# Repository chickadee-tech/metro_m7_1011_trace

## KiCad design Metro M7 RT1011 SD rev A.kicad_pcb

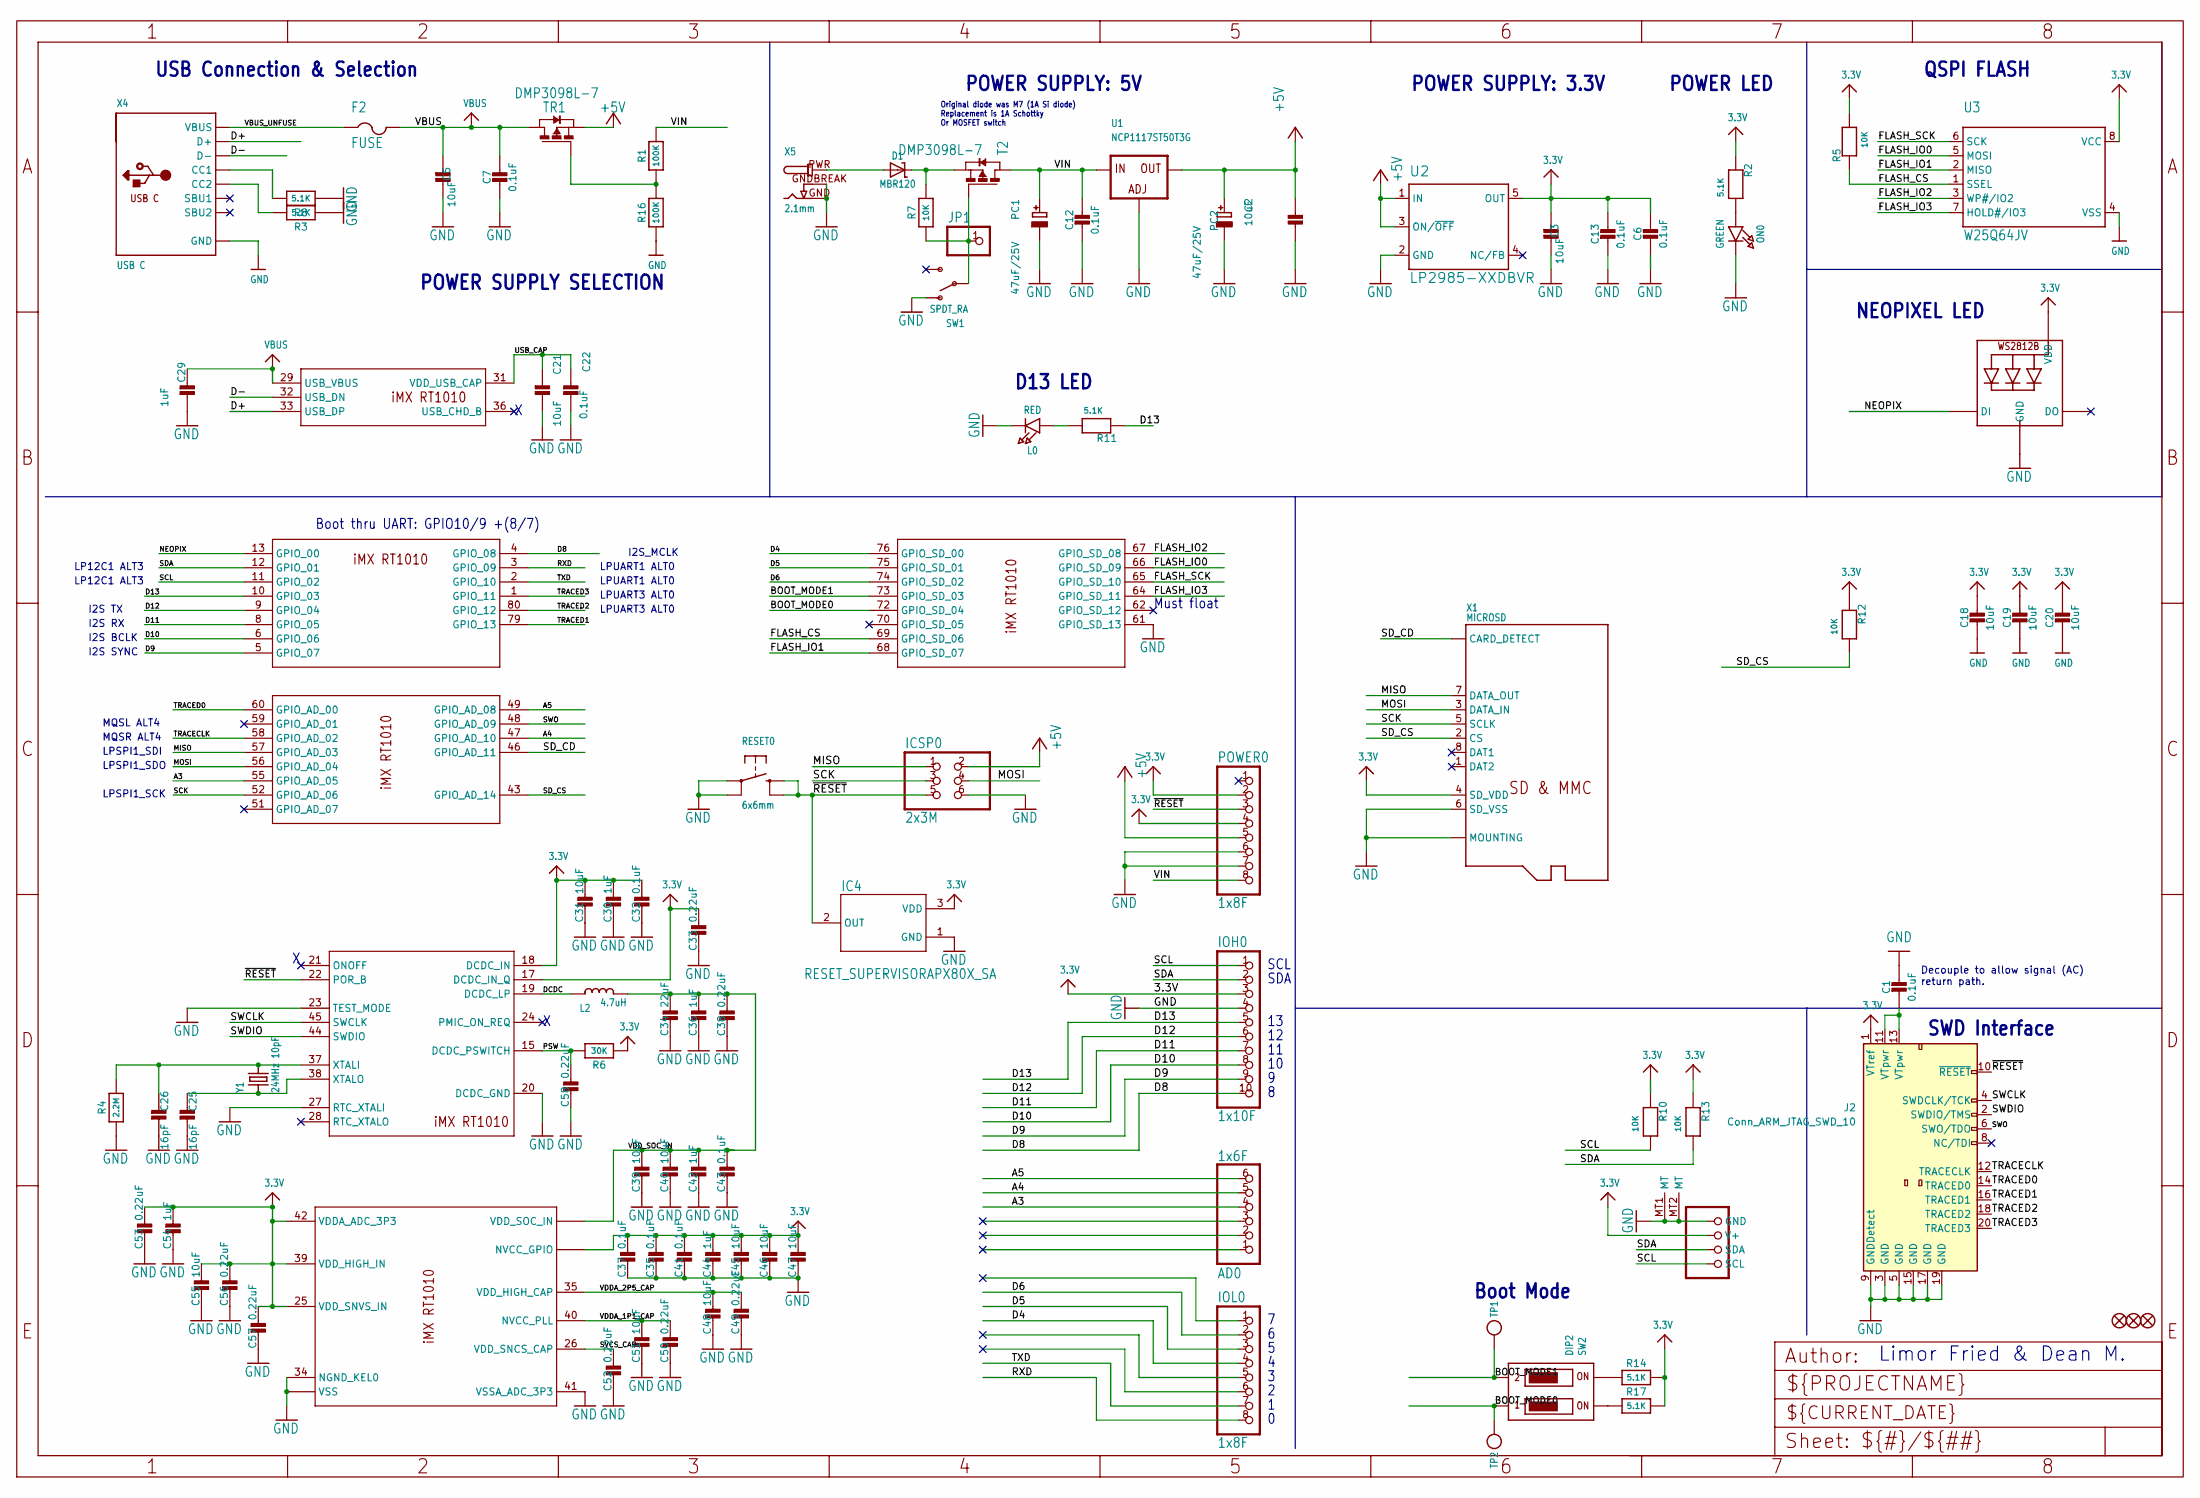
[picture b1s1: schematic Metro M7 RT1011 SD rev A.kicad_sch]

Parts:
AD0: 1x6F; 1X06_OVALWAVE
C1, C6, C7, C12, C13, C22, C32, C35, C37, C41, C43: 0.1uF; 0603-NO
C2, C3, C5, C18, C19, C20, C21, C31, C39, C40, C45, C46, C47, C48, C51, C55: 10uF; 0805-NO
C25, C26: 16pF; 0603-NO
C29, C30, C36, C42, C44, C54: 1uF; 0603-NO
C33, C38, C49, C50, C52, C53, C56, C57, C58: 0.22uF; 0603-NO
C34: 22uF; 0805-NO
CONN1: STEMMA_I2C_QT; JST_SH4
D1: MBR120; SOD-123
F2: FUSE; R1206
FD1, FD2, FD3: FIDUCIAL_1MM
IC2: IMX_RT1010; QFP50P1400X1400X160-80N
IC4: RESET_SUPERVISORAPX80X_SA; SOT23-WIDE
ICSP0: 2x3M; 2X03_ROUND_70MIL
IOH0: 1x10F; 1X10_OVALWAVE
IOL0: 1x8F; 1X08_OVALWAVE
J2: Conn_ARM_JTAG_SWD_10; PinHeader_2x10_P1.27mm_Vertical_SMD
JP1: HEADER-1X1ROUND; 1X01_ROUND
L0: RED; CHIPLED_0603_NOOUTLINE
L2: 4.7uH; INDUCTOR_1007
LED1: WS2812B_3535FULL; LED3535_FULLPADS
ON0: GREEN; CHIPLED_0603_NOOUTLINE
PC1, PC2: 47uF/25V; PANASONIC_D
POWER0: 1x8F; 1X08_OVALWAVE
R1, R16: 100K; 0603-NO
R2, R3, R8, R11, R14, R17: 5.1K; 0603-NO
R4: 2.2M; 0603-NO
R5, R7, R10, R12, R13: 10K; 0603-NO
R6: 30K; 0603-NO
RESET0: 6x6mm; 6MMX6MM_TACTILE_SMT
SW1: SPDT_RA; SPDT_SMT_SSSS811101
SW2: DIP2; DIPSWITCH_2PIN
T2: DMP3098L-7; SOT-23
TP1, TP2: TESTPOINTROUND1.5MM; TESTPOINT_ROUND_1.5MM
TR1: DMP3098L-7; SOT-23
U1: NCP1117ST50T3G; SOT223-R
U2: LP2985-XXDBVR; SOT23-DBV
U3: W25Q64JV; SOIC8_208MIL
X1: MICROSD
X4: USB C; USB_C_CUSB31-CFM2AX-01-X
X5: 2.1mm; DCJACK_2MM_PTH
Y1: 24MHz 10pF; CRYSTAL_2.5X2

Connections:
3.3V: C3.2, C6.2, C13.1, C18.1, C19.1, C20.1, C30.1, C31.1, C32.1, C33.1, C35.1, C37.1, C41.1, C44.1, C45.1, C46.1, C47.1, C53.1, C54.1, C55.1, C56.1, C57.1, CONN1.2 (V+), IC2.7 (NVCC_GPIO), IC2.17 (DCDC_IN_Q), IC2.18 (DCDC_IN), IC2.25 (VDD_SNVS_IN), IC2.39 (VDD_HIGH_IN), IC2.42 (VDDA_ADC_3P3), IC2.50 (NVCC_GPIO), IC2.63 (NVCC_GPIO), IC2.71 (NVCC_GPIO), IC4.3 (VDD), IOH0.3, J2.1 (VTref), LED1.2 (VDD), POWER0.2, POWER0.4, R2.1, R5.2, R6.1, R10.1, R12.1, R13.1, R14.2, R17.2, U2.5 (OUT), U3.8 (VCC), X1.4 (SD_VDD)
+5V: C2.2, ICSP0.2, PC2.+, POWER0.5, TR1.2 (S), U1.2 (OUT), U1.4 (OUT), U2.1 (IN), U2.3 (ON/~OFF)
/A3: AD0.4, IC2.55 (GPIO_AD_05)
/A4: AD0.5, IC2.47 (GPIO_AD_10)
/A5: AD0.6, IC2.49 (GPIO_AD_08)
/BOOT_MODE0: IC2.72 (GPIO_SD_04), SW2.1OFF, TP2.P$1
/BOOT_MODE1: IC2.73 (GPIO_SD_03), SW2.2OFF, TP1.P$1
/D4: IC2.76 (GPIO_SD_00), IOL0.4
/D5: IC2.75 (GPIO_SD_01), IOL0.3
/D6: IC2.74 (GPIO_SD_02), IOL0.2
/D8: IC2.4 (GPIO_08), IOH0.10
/D9: IC2.5 (GPIO_07), IOH0.9
/D10: IC2.6 (GPIO_06), IOH0.8
/D11: IC2.8 (GPIO_05), IOH0.7
/D12: IC2.9 (GPIO_04), IOH0.6
/D13: IC2.10 (GPIO_03), IOH0.5, R11.1
/D+: IC2.33 (USB_DP), X4.A6 (D+), X4.B6 (D+)
/D-: IC2.32 (USB_DN), X4.A7 (D-), X4.B7 (D-)
/DCDC: IC2.19 (DCDC_LP), L2.P$1 (1)
/FLASH_CS: IC2.69 (GPIO_SD_06), R5.1, U3.1 (SSEL)
/FLASH_IO0: IC2.66 (GPIO_SD_09), U3.5 (MOSI)
/FLASH_IO1: IC2.68 (GPIO_SD_07), U3.2 (MISO)
/FLASH_IO2: IC2.67 (GPIO_SD_08), U3.3 (WP#/IO2)
/FLASH_IO3: IC2.64 (GPIO_SD_11), U3.7 (HOLD#/IO3)
/FLASH_SCK: IC2.65 (GPIO_SD_10), U3.6 (SCK)
/MISO: IC2.57 (GPIO_AD_03), ICSP0.1, X1.7 (DATA_OUT)
/MOSI: IC2.56 (GPIO_AD_04), ICSP0.4, X1.3 (DATA_IN)
/NEOPIX: IC2.13 (GPIO_00), LED1.1 (DI)
/PSW: C58.1, IC2.15 (DCDC_PSWITCH), R6.2
/RXD: IC2.3 (GPIO_09), IOL0.8
/SCK: IC2.52 (GPIO_AD_06), ICSP0.3, X1.5 (SCLK)
/SCL: CONN1.4 (SCL), IC2.11 (GPIO_02), IOH0.1, R10.2
/SDA: CONN1.3 (SDA), IC2.12 (GPIO_01), IOH0.2, R13.2
/SD_CD: IC2.46 (GPIO_AD_11), X1.CD1 (CARD_DETECT), X1.CD2 (CARD_DETECT)
/SD_CS: IC2.43 (GPIO_AD_14), R12.2, X1.2 (CS)
/SVCS_CAP: C52.1, IC2.26 (VDD_SNCS_CAP)
/SWCLK: IC2.45 (SWCLK), J2.4 (SWDCLK/TCK)
/SWDIO: IC2.44 (SWDIO), J2.2 (SWDIO/TMS)
/SWO: IC2.48 (GPIO_AD_09), J2.6 (SWO/TDO)
/TRACECLK: IC2.58 (GPIO_AD_02), J2.12 (TRACECLK)
/TRACED0: IC2.60 (GPIO_AD_00), J2.14 (TRACED0)
/TRACED1: IC2.79 (GPIO_13), J2.16 (TRACED1)
/TRACED2: IC2.80 (GPIO_12), J2.18 (TRACED2)
/TRACED3: IC2.1 (GPIO_11), J2.20 (TRACED3)
/TXD: IC2.2 (GPIO_10), IOL0.7
/USB_CAP: C21.2, C22.1, IC2.31 (VDD_USB_CAP)
/VBUS_UNFUSE: F2.1, X4.A4B9 (VBUS), X4.B4A9 (VBUS)
/VDDA_1P1_CAP: C50.1, C51.1, IC2.40 (NVCC_PLL)
/VDDA_2P5_CAP: C48.1, C49.1, IC2.35 (VDD_HIGH_CAP)
/VDD_SOC_IN: C34.1, C36.1, C38.1, C39.1, C40.1, C42.1, C43.1, IC2.14 (VDD_SOC_IN), IC2.53 (VDD_SOC_IN), IC2.77 (VDD_SOC_IN), L2.P$2 (2)
/VIN: C12.1, PC1.+, POWER0.8, R1.2, T2.1 (D), U1.3 (IN)
/~RESET: IC2.22 (POR_B), IC4.2 (OUT), ICSP0.5, J2.10 (~RESET), POWER0.3, RESET0.B (S), RESET0.B' (S1)
GND: C1.1, C2.1, C3.1, C5.1, C6.1, C7.2, C12.2, C13.2, C18.2, C19.2, C20.2, C21.1, C22.2, C25.2, C26.2, C29.2, C30.2, C31.2, C32.2, C33.2, C34.2, C35.2, C36.2, C37.2, C38.2, C39.2, C40.2, C41.2, C42.2, C43.2, C44.2, C45.2, C46.2, C47.2, C48.2, C49.2, C50.2, C51.2, C52.2, C53.2, C54.2, C55.2, C56.2, C57.2, C58.2, CONN1.1 (GND), CONN1.MT1 (MT), CONN1.MT2 (MT), IC2.16 (VSS), IC2.20 (DCDC_GND), IC2.23 (TEST_MODE), IC2.27 (RTC_XTALI), IC2.30 (VSS), IC2.34 (NGND_KEL0), IC2.41 (VSSA_ADC_3P3), IC2.54 (VSS), IC2.61 (GPIO_SD_13), IC2.78 (VSS), IC4.1 (GND), ICSP0.6, IOH0.4, J2.3 (GND), J2.5 (GND), J2.9 (GNDDetect), J2.15 (GND), J2.17 (GND), J2.19 (GND), L0.C, LED1.4 (GND), ON0.C, PC1.-, PC2.-, POWER0.6, POWER0.7, R3.1, R4.1, R8.1, R16.1, RESET0.A, RESET0.A' (P1), SW1.A (O), U1.1 (ADJ), U2.2 (GND), U3.4 (VSS), X1.6 (SD_VSS), X1.MT1 (MOUNTING), X1.MT2 (MOUNTING), X4.A1B12 (GND), X4.B1A12 (GND), X5.GND, X5.GNDBREAK
unnamed: C1.2, J2.11 (VTpwr), J2.13 (VTpwr)
unnamed: D1.A, X5.PWR
unnamed: C26.1, IC2.37 (XTALI), R4.2, Y1.3 (2)
unnamed: C25.1, IC2.38 (XTALO), Y1.1
unnamed: L0.A, R11.2
unnamed: ON0.A, R2.2
unnamed: R14.1, SW2.2ON
unnamed: R17.1, SW2.1ON
unnamed: JP1.1, R7.1, SW1.B, T2.3 (G)
unnamed: D1.C, R7.2, T2.2 (S)
unnamed: R1.1, R16.2, TR1.3 (G)
unnamed: R8.2, X4.A5 (CC1)
unnamed: R3.2, X4.B5 (CC2)
VBUS: C5.2, C7.1, C29.1, F2.2, IC2.29 (USB_VBUS), TR1.1 (D)

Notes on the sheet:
LPUART1 ALT0
I2S_MCLK
Must float
POWER SUPPLY SELECTION
LPUART3 ALT0
LPSPI1_SDI
LPSPI1_SDO
Decouple to allow signal (AC) return path.
USB Connection & Selection
Original diode was M7 (1A Si diode) Replacement is 1A Schottky Or MOSFET switch
Boot Mode
I2S SYNC
LP12C1 ALT3
SCL
I2S BCLK
QSPI FLASH
I2S RX
D13 LED
MQSL ALT4
MQSR ALT4
Boot thru UART: GPIO10/9 +(8/7)
I2S TX
SWD Interface
POWER LED
NEOPIXEL LED
POWER SUPPLY: 5V
Limor Fried & Dean M.
LPSPI1_SCK
POWER SUPPLY: 3.3V
SDA

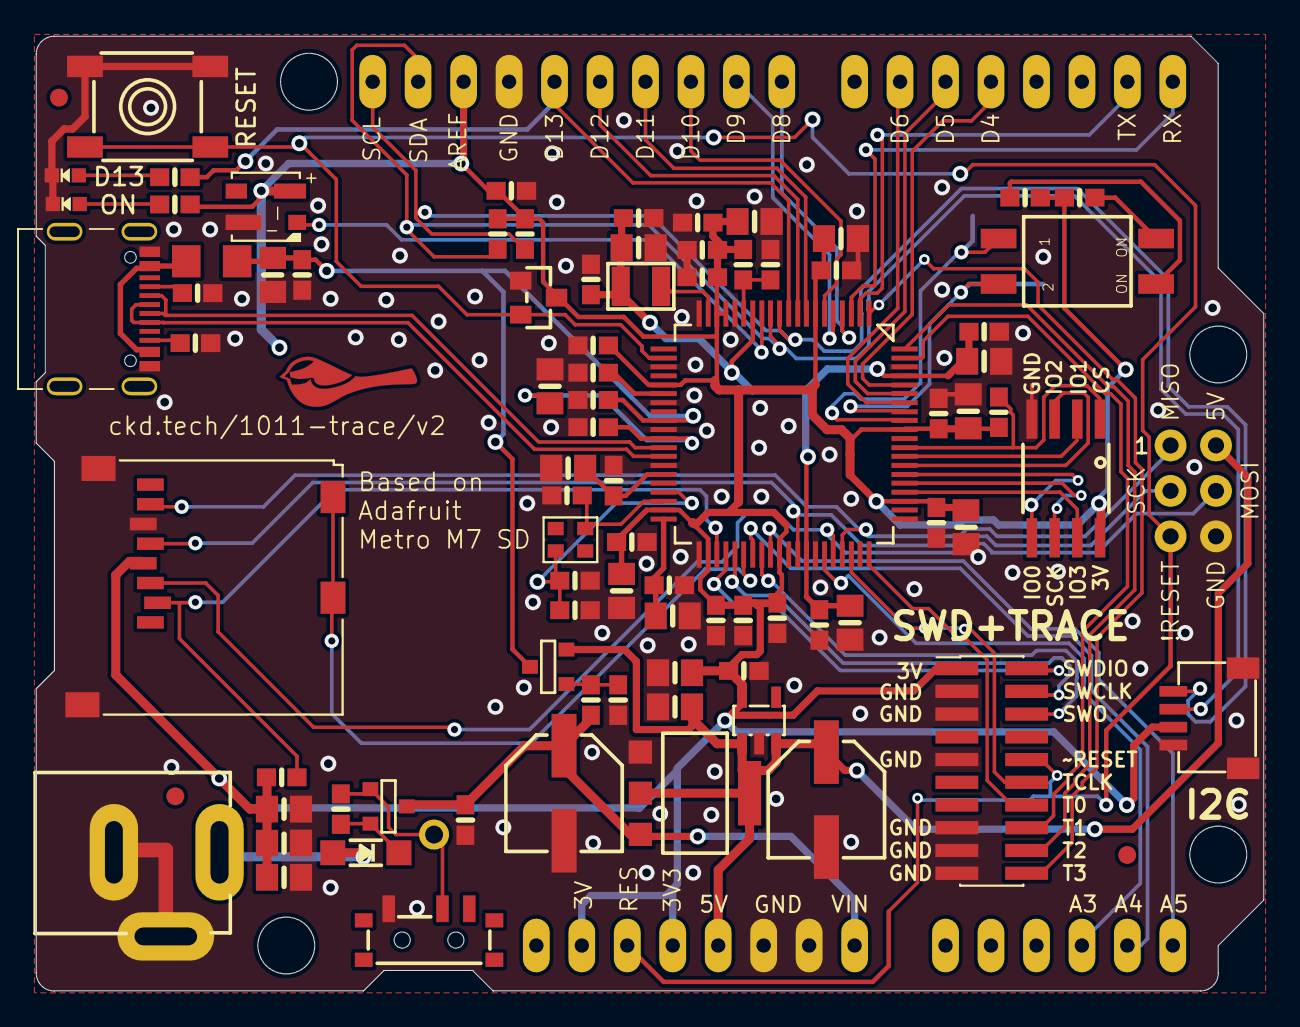
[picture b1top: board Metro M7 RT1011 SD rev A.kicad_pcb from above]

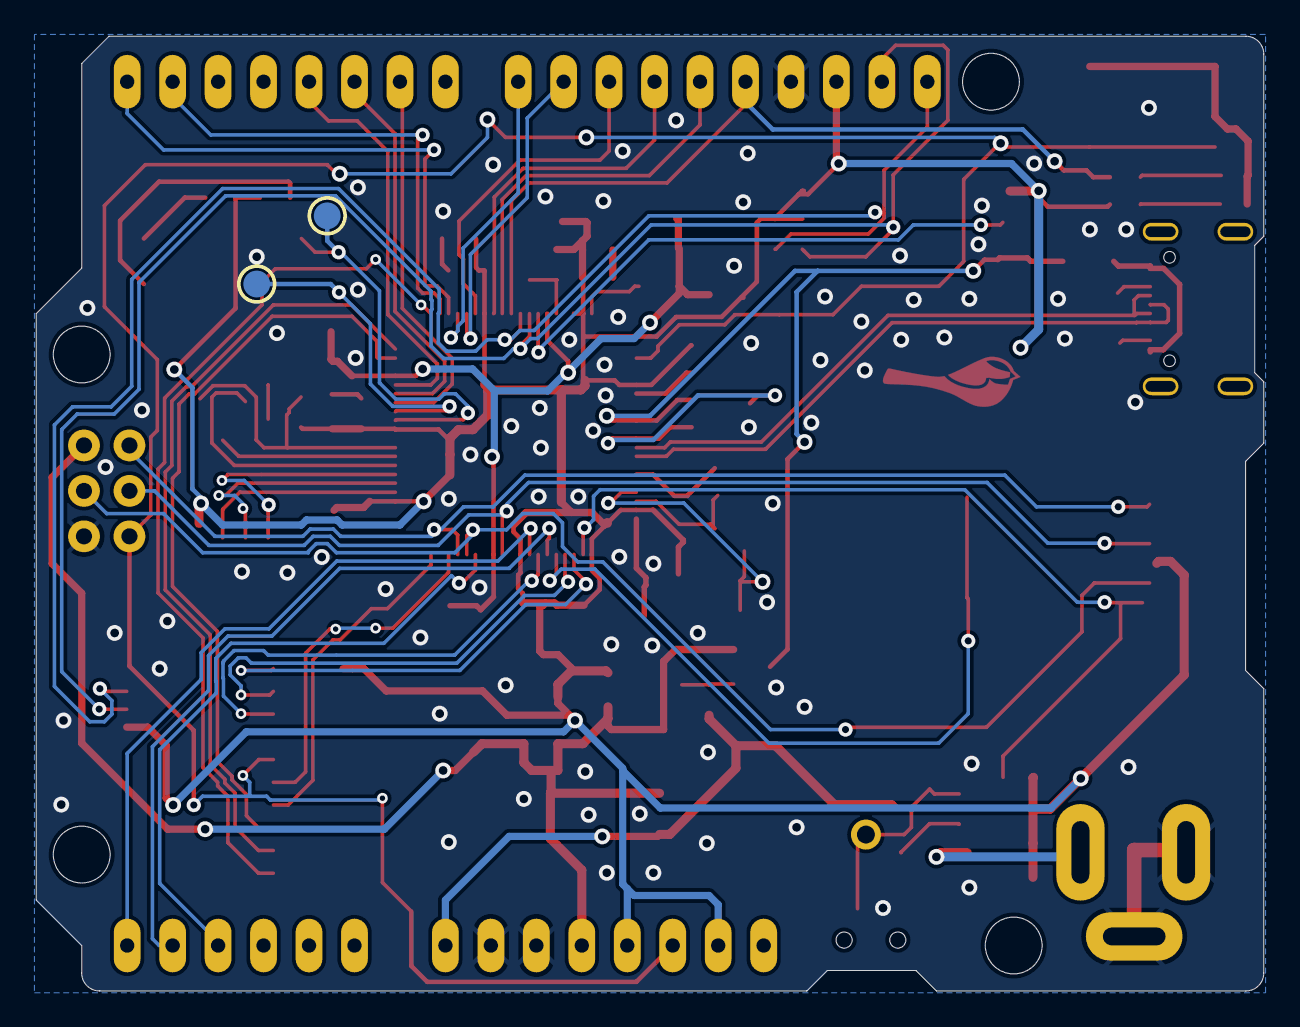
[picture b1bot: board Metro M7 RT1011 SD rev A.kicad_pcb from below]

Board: 2 copper layers, 68.6 x 53.3 mm, 100 parts (3 on the bottom side), 66 nets.

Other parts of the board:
@HOLE0, @HOLE1, @HOLE2, @HOLE3: (no value)
U$12: M7_RT1011SD_TOP
U$19: M7_RT1011SD_BOT

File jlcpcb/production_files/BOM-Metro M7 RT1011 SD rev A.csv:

Comment,Designator,Footprint,LCSC
30K,R6,0603-NO,C100001
SPDT_RA,SW1,SPDT_SMT_SSSS811101,C109335
MICROSD,X1,MICROSD,C125617
0.1uF,"C12,C13,C22,C32,C35,C37,C41,C43,C6,C7",0603-NO,C14663
DMP3098L-7,"T2,TR1",SOT-23,C150492
NCP1117ST50T3G,U1,SOT223-R,C156196
RESET_SUPERVISORAPX80X_SA,IC4,SOT23-WIDE,C156335
IMX_RT1010,IC2,QFP50P1400X1400X160-80N,C1575810
1uF,"C29,C30,C36,C42,C44,C54",0603-NO,C15849
10uF,"C18,C19,C2,C20,C21,C3,C31,C39,C40,C45,C46,C47,C48,C5,C51,C55",0805-NO,C15850
USB C,X4,USB_C_CUSB31-CFM2AX-01-X,C165948
0.22uF,"C33,C38,C49,C50,C52,C53,C56,C57,C58",0603-NO,C21120
4.7uH,L2,INDUCTOR_1007,C223195
RED,L0,CHIPLED_0603_NOOUTLINE,C2286
2.2M,R4,0603-NO,C22938
5.1K,"R11,R14,R17,R2,R3,R8",0603-NO,C23186
24MHz 10pF,Y1,CRYSTAL_2.5X2,C255953
100K,"R1,R16",0603-NO,C25803
10K,"R10,R12,R13,R5,R7",0603-NO,C25804
6x6mm,RESET0,6MMX6MM_TACTILE_SMT,C2686883
FUSE,F2,R1206,C269104
STEMMA_I2C_QT,CONN1,JST_SH4,C2845363
22uF,C34,0805-NO,C29277
2.1mm,X5,DCJACK_2MM_PTH,C381116
DIP2,SW2,DIPSWITCH_2PIN,C489174
16pF,"C25,C26",0603-NO,C527060
Conn_ARM_JTAG_SWD_10,J2,PinHeader_2x10_P1.27mm_Vertical_SMD,C59981
MBR120,D1,SOD-123,C668956
GREEN,ON0,CHIPLED_0603_NOOUTLINE,C72043
W25Q64JV,U3,SOIC8_208MIL,C83140
LP2985-XXDBVR,U2,SOT23-DBV,C841192
47uF/25V,"PC1,PC2",PANASONIC_D,C97807
